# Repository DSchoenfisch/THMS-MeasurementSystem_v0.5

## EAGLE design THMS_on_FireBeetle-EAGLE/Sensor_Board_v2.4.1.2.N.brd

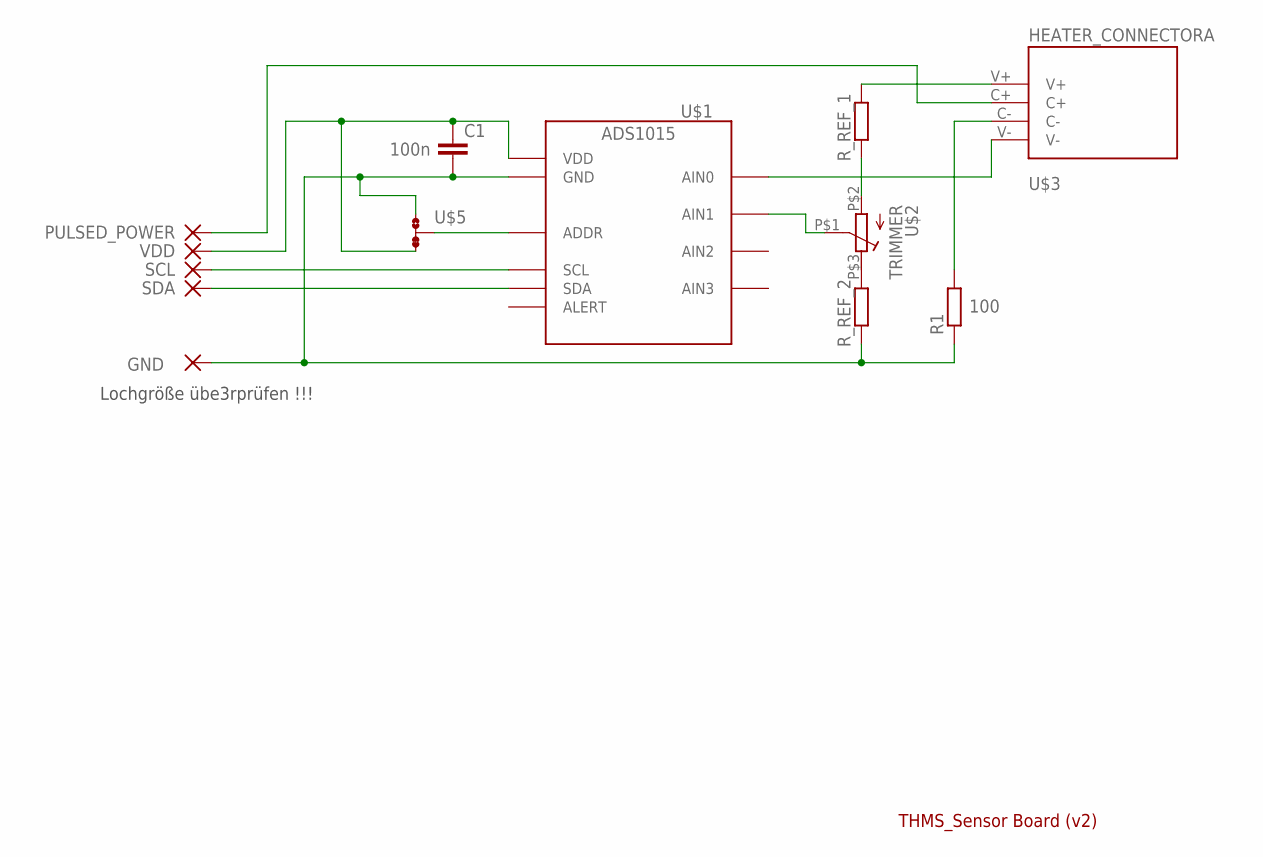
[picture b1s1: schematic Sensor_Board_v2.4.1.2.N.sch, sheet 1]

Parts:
C1: 100n; C0201
GND: 2,54/1,1
PULSED_POWER: SMD_PADSMD05-2(STPOO_DEFINED); SMD0,5-2(STOP_DEFINED)
R1: 100; R0402
R_REF_1, R_REF_2: 0; R0201
SCL: SMD_PADSMD05-2(STPOO_DEFINED); SMD0,5-2(STOP_DEFINED)
SDA: SMD_PADSMD05-2(STPOO_DEFINED); SMD0,5-2(STOP_DEFINED)
U$1: ADS1015; X2QFN10
U$2: TRIMMER; 2MM
U$3: HEATER_CONNECTORA; CONECTION_GATES
U$5: 0R-JUMP-1CON; D0R-JMP(D)
VDD: SMD_PADSMD05-2(STPOO_DEFINED); SMD0,5-2(STOP_DEFINED)

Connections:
GND: C1.2, GND.1, R1.1, R_REF_2.1, U$1.P$3 (GND), U$5.1; also elsewhere on the board
unnamed: R_REF_2.2, U$2.P$3 (A)
unnamed: SCL.1, U$1.P$10 (SCL)
unnamed: SDA.1, U$1.P$9 (SDA)
unnamed: R_REF_1.1, U$2.P$2 (E)
unnamed: R_REF_1.2, U$3.V+
unnamed: R1.2, U$3.C-
unnamed: PULSED_POWER.1, U$3.C+
unnamed: U$1.P$4 (AIN0), U$3.V-
unnamed: U$1.P$1 (ADDR), U$5.2
unnamed: U$1.P$5 (AIN1), U$2.P$1 (S)
VDD: C1.1, U$1.P$8 (VDD), U$5.3, VDD.1; also elsewhere on the board

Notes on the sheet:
Lochgröße übe3rprüfen !!!
THMS_Sensor Board (v2)

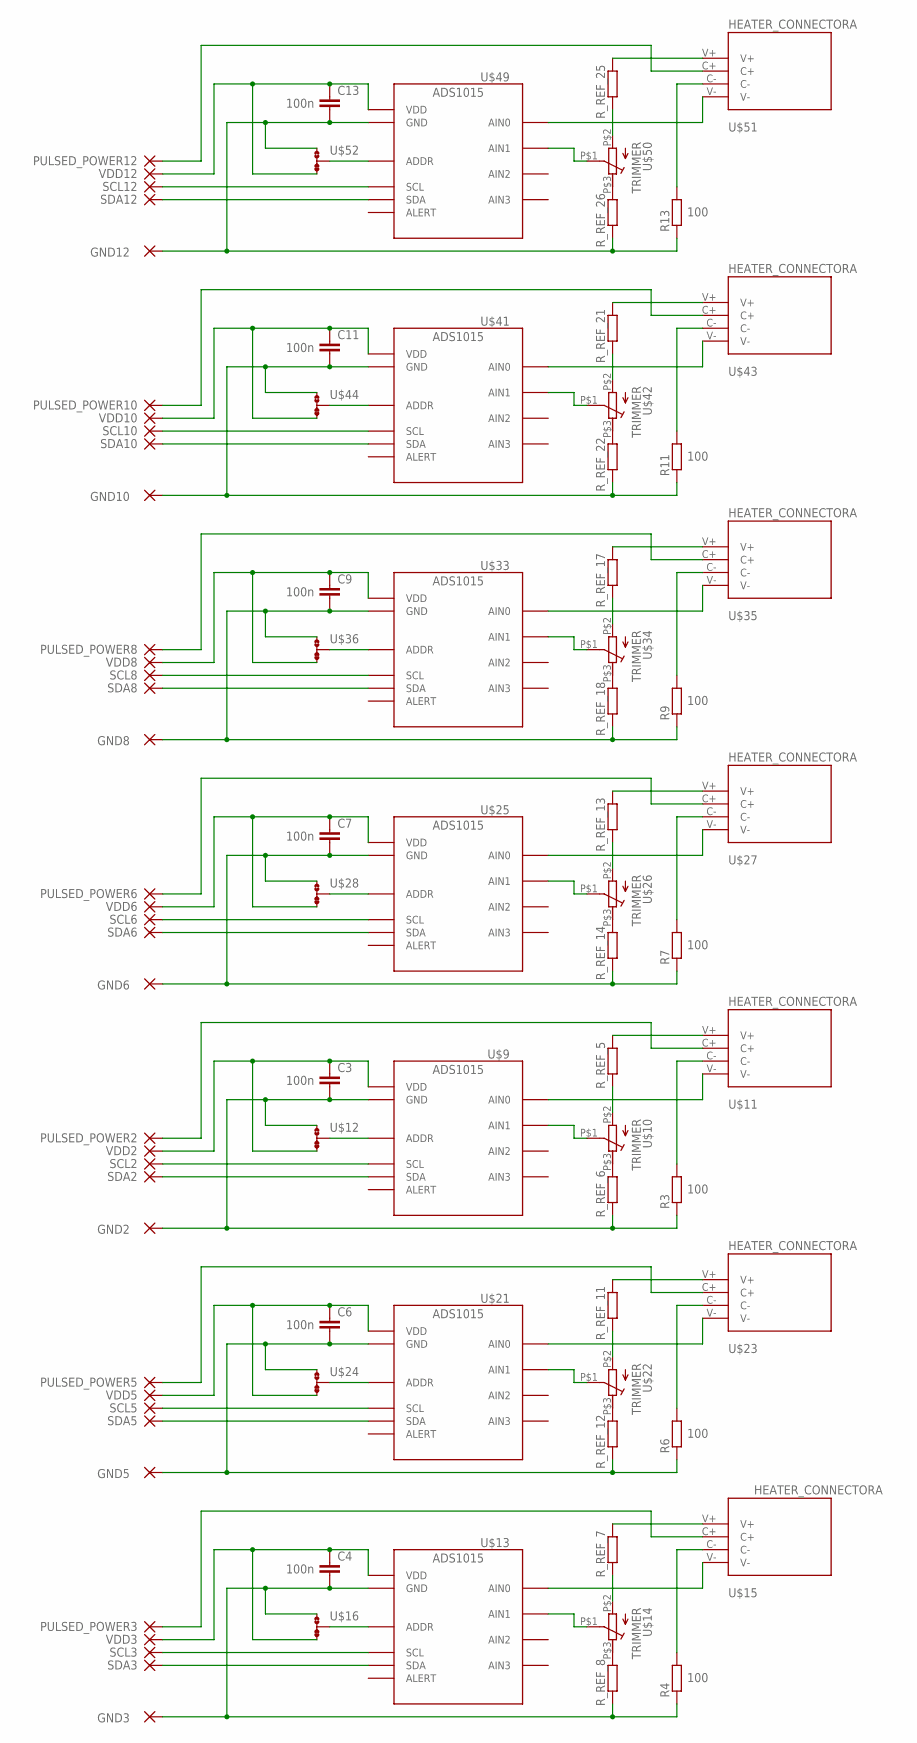
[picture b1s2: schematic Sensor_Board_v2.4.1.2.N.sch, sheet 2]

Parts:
C3, C4, C6, C7, C9, C11, C13: 100n; C0201
GND2, GND3, GND5, GND6, GND8, GND10, GND12: 2,54/1,1
PULSED_POWER2, PULSED_POWER3, PULSED_POWER5, PULSED_POWER6, PULSED_POWER8, PULSED_POWER10, PULSED_POWER12: SMD_PADSMD05-2(STPOO_DEFINED); SMD0,5-2(STOP_DEFINED)
R3, R4, R6, R7, R9, R11, R13: 100; R0402
R_REF_5, R_REF_6, R_REF_7, R_REF_8, R_REF_11, R_REF_12, R_REF_13, R_REF_14, R_REF_17, R_REF_18, R_REF_21, R_REF_22, R_REF_25, R_REF_26: 0; R0201
SCL2, SCL3, SCL5, SCL6, SCL8, SCL10, SCL12: SMD_PADSMD05-2(STPOO_DEFINED); SMD0,5-2(STOP_DEFINED)
SDA2, SDA3, SDA5, SDA6, SDA8, SDA10, SDA12: SMD_PADSMD05-2(STPOO_DEFINED); SMD0,5-2(STOP_DEFINED)
U$9, U$13, U$21, U$25, U$33, U$41, U$49: ADS1015; X2QFN10
U$10, U$14, U$22, U$26, U$34, U$42, U$50: TRIMMER; 2MM
U$11, U$15, U$23, U$27, U$35, U$43, U$51: HEATER_CONNECTORA; CONECTION_GATES
U$12, U$16, U$24, U$28, U$36, U$44, U$52: 0R-JUMP-1CON; D0R-JMP(D)
VDD2, VDD3, VDD5, VDD6, VDD8, VDD10, VDD12: SMD_PADSMD05-2(STPOO_DEFINED); SMD0,5-2(STOP_DEFINED)

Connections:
GND: C3.2, C4.2, C6.2, C7.2, C9.2, C11.2, C13.2, GND2.1, GND3.1, GND5.1, GND6.1, GND8.1, GND10.1, GND12.1, R3.1, R4.1, R6.1, R7.1, R9.1, R11.1, R13.1, R_REF_6.1, R_REF_8.1, R_REF_12.1, R_REF_14.1, R_REF_18.1, R_REF_22.1, R_REF_26.1, U$9.P$3 (GND), U$12.1, U$13.P$3 (GND), U$16.1, U$21.P$3 (GND), U$24.1, U$25.P$3 (GND), U$28.1, U$33.P$3 (GND), U$36.1, U$41.P$3 (GND), U$44.1, U$49.P$3 (GND), U$52.1; also elsewhere on the board
unnamed: SCL2.1, U$9.P$10 (SCL)
unnamed: SDA2.1, U$9.P$9 (SDA)
unnamed: R_REF_5.2, U$11.V+
unnamed: R3.2, U$11.C-
unnamed: U$9.P$4 (AIN0), U$11.V-
unnamed: PULSED_POWER2.1, U$11.C+
unnamed: U$9.P$5 (AIN1), U$10.P$1 (S)
unnamed: U$9.P$1 (ADDR), U$12.2
unnamed: R_REF_6.2, U$10.P$3 (A)
unnamed: R_REF_5.1, U$10.P$2 (E)
unnamed: SCL3.1, U$13.P$10 (SCL)
unnamed: SDA3.1, U$13.P$9 (SDA)
unnamed: R_REF_7.2, U$15.V+
unnamed: R4.2, U$15.C-
unnamed: U$13.P$4 (AIN0), U$15.V-
unnamed: PULSED_POWER3.1, U$15.C+
unnamed: U$13.P$5 (AIN1), U$14.P$1 (S)
unnamed: U$13.P$1 (ADDR), U$16.2
unnamed: R_REF_8.2, U$14.P$3 (A)
unnamed: R_REF_7.1, U$14.P$2 (E)
unnamed: SCL5.1, U$21.P$10 (SCL)
unnamed: SDA5.1, U$21.P$9 (SDA)
unnamed: R_REF_11.2, U$23.V+
unnamed: R6.2, U$23.C-
unnamed: U$21.P$4 (AIN0), U$23.V-
unnamed: PULSED_POWER5.1, U$23.C+
unnamed: U$21.P$5 (AIN1), U$22.P$1 (S)
unnamed: U$21.P$1 (ADDR), U$24.2
unnamed: R_REF_12.2, U$22.P$3 (A)
unnamed: R_REF_11.1, U$22.P$2 (E)
unnamed: SCL6.1, U$25.P$10 (SCL)
unnamed: SDA6.1, U$25.P$9 (SDA)
unnamed: R_REF_13.2, U$27.V+
unnamed: R7.2, U$27.C-
unnamed: U$25.P$4 (AIN0), U$27.V-
unnamed: PULSED_POWER6.1, U$27.C+
unnamed: U$25.P$5 (AIN1), U$26.P$1 (S)
unnamed: U$25.P$1 (ADDR), U$28.2
unnamed: R_REF_14.2, U$26.P$3 (A)
unnamed: R_REF_13.1, U$26.P$2 (E)
unnamed: SCL8.1, U$33.P$10 (SCL)
unnamed: SDA8.1, U$33.P$9 (SDA)
unnamed: R_REF_17.2, U$35.V+
unnamed: R9.2, U$35.C-
unnamed: U$33.P$4 (AIN0), U$35.V-
unnamed: PULSED_POWER8.1, U$35.C+
unnamed: U$33.P$5 (AIN1), U$34.P$1 (S)
unnamed: U$33.P$1 (ADDR), U$36.2
unnamed: R_REF_18.2, U$34.P$3 (A)
unnamed: R_REF_17.1, U$34.P$2 (E)
unnamed: SCL10.1, U$41.P$10 (SCL)
unnamed: SDA10.1, U$41.P$9 (SDA)
unnamed: R_REF_21.2, U$43.V+
unnamed: R11.2, U$43.C-
unnamed: U$41.P$4 (AIN0), U$43.V-
unnamed: PULSED_POWER10.1, U$43.C+
unnamed: U$41.P$5 (AIN1), U$42.P$1 (S)
unnamed: U$41.P$1 (ADDR), U$44.2
unnamed: R_REF_22.2, U$42.P$3 (A)
unnamed: R_REF_21.1, U$42.P$2 (E)
unnamed: SCL12.1, U$49.P$10 (SCL)
unnamed: SDA12.1, U$49.P$9 (SDA)
unnamed: R_REF_25.2, U$51.V+
unnamed: R13.2, U$51.C-
unnamed: U$49.P$4 (AIN0), U$51.V-
unnamed: PULSED_POWER12.1, U$51.C+
unnamed: U$49.P$5 (AIN1), U$50.P$1 (S)
unnamed: U$49.P$1 (ADDR), U$52.2
unnamed: R_REF_26.2, U$50.P$3 (A)
unnamed: R_REF_25.1, U$50.P$2 (E)
VDD: C3.1, C4.1, C6.1, C7.1, C9.1, C11.1, C13.1, U$9.P$8 (VDD), U$12.3, U$13.P$8 (VDD), U$16.3, U$21.P$8 (VDD), U$24.3, U$25.P$8 (VDD), U$28.3, U$33.P$8 (VDD), U$36.3, U$41.P$8 (VDD), U$44.3, U$49.P$8 (VDD), U$52.3, VDD2.1, VDD3.1, VDD5.1, VDD6.1, VDD8.1, VDD10.1, VDD12.1; also elsewhere on the board

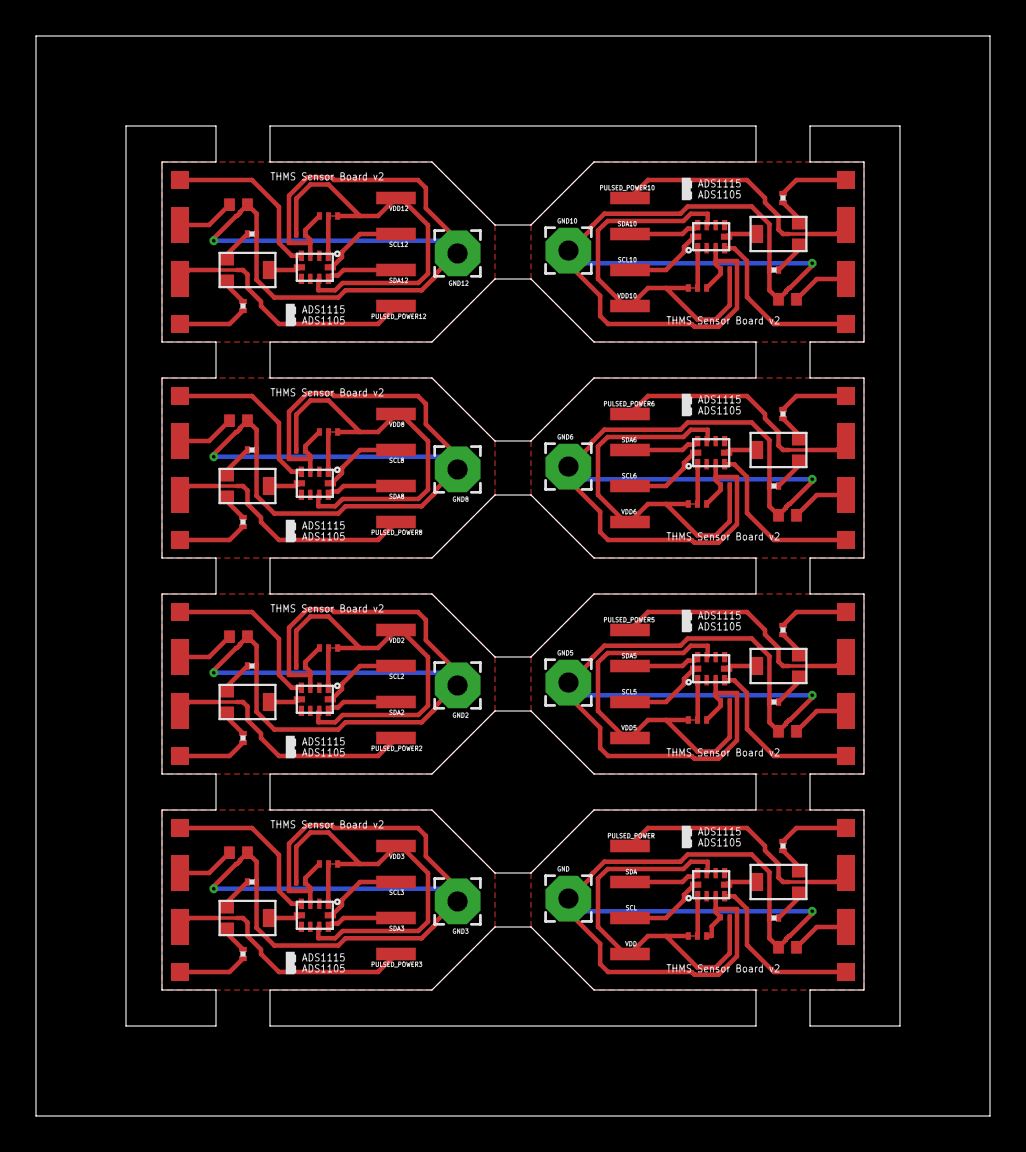
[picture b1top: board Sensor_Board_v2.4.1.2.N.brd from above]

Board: 2 copper layers, 53.0 x 60.0 mm, 104 parts (0 on the bottom side), 82 nets.

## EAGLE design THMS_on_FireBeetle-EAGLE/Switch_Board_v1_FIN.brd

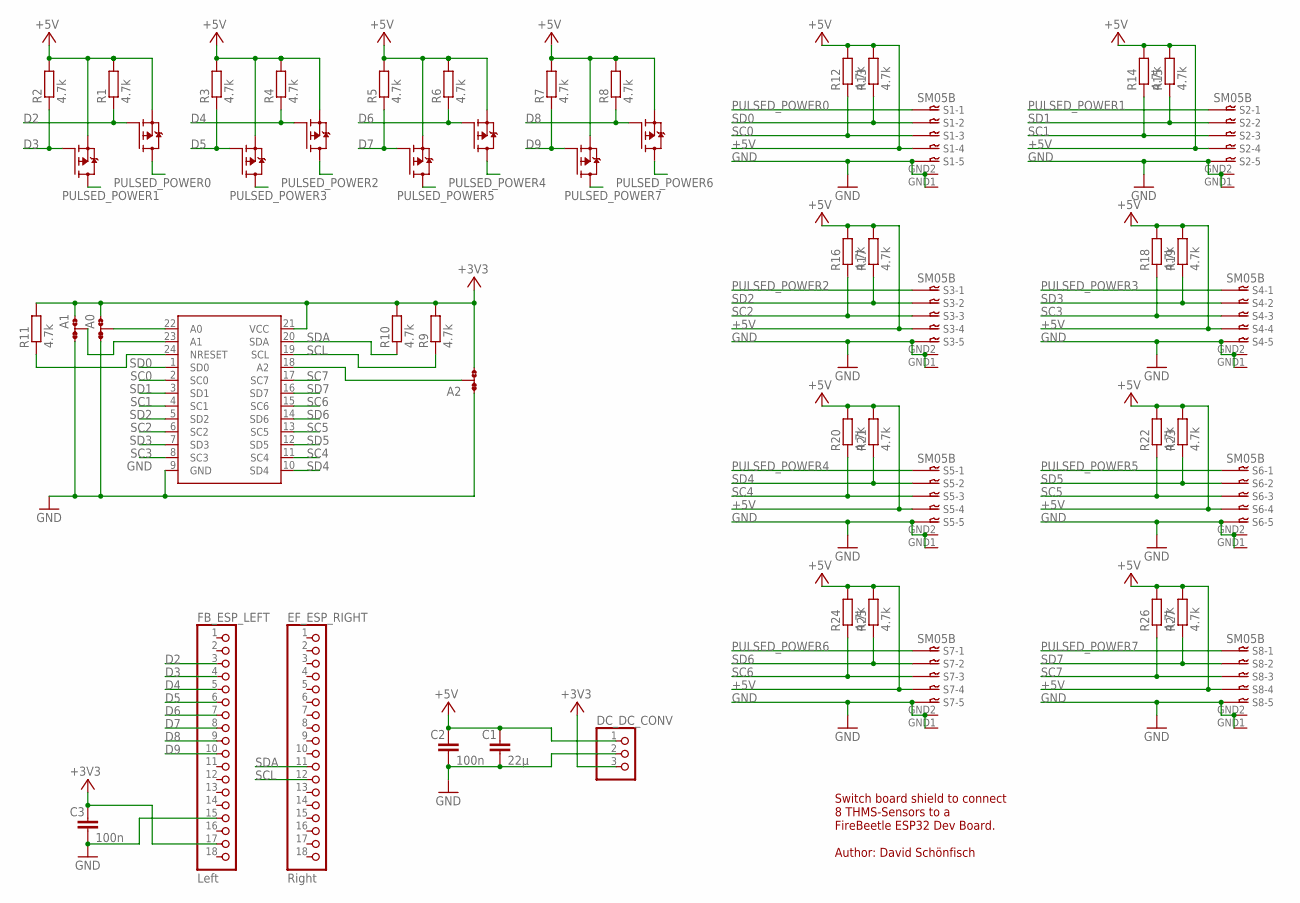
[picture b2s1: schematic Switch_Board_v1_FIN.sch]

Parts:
A0, A1, A2: 0R-JUMP-1CON; D0R-JMP(D)
C1: 22µ; C0603
C2, C3: 100n; C0603
DC_DC_CONV: 0; 1X03
EF_ESP_RIGHT: Right; 1X18
FB_ESP_LEFT: Left; 1X18
R1, R2, R3, R4, R5, R6, R7, R8, R9, R10, R11, R12, R13, R14, R15, R16, R17, R18, R19, R20, R21, R22, R23, R24, R25, R26, R27: 4.7k; R0603
S1, S2, S3, S4, S5, S6, S7, S8: SM05B
U$1: TCA9548PVQFN; S-PVQFN-N24
U$2, U$3, U$4, U$5: UM6J1N; SOT363_INFINEON

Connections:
+3V3: A0.1, A1.1, A2.1, C3.1, DC_DC_CONV.3, FB_ESP_LEFT.17, R9.2, R10.2, R11.2, U$1.21 (VCC)
+5V: C1.1, C2.1, DC_DC_CONV.1, R1.2, R2.2, R3.2, R4.2, R5.2, R6.2, R7.2, R8.2, R12.2, R13.2, R14.2, R15.2, R16.2, R17.2, R18.2, R19.2, R20.2, R21.2, R22.2, R23.2, R24.2, R25.2, R26.2, R27.2, S1.4 (1), S2.4 (1), S3.4 (1), S4.4 (1), S5.4 (1), S6.4 (1), S7.4 (1), S8.4 (1), U$2.1 (S), U$2.4 (S), U$3.1 (S), U$3.4 (S), U$4.1 (S), U$4.4 (S), U$5.1 (S), U$5.4 (S)
A0: A0.2, U$1.22 (A0)
A1: A1.2, U$1.23 (A1)
A2: A2.2, U$1.18 (A2)
D2: FB_ESP_LEFT.3, R1.1, U$2.2 (G)
D3: FB_ESP_LEFT.4, R2.1, U$2.5 (G)
D4: FB_ESP_LEFT.5, R4.1, U$3.2 (G)
D5: FB_ESP_LEFT.6, R3.1, U$3.5 (G)
D6: FB_ESP_LEFT.7, R6.1, U$4.2 (G)
D7: FB_ESP_LEFT.8, R5.1, U$4.5 (G)
D8: FB_ESP_LEFT.9, R8.1, U$5.2 (G)
D9: FB_ESP_LEFT.10, R7.1, U$5.5 (G)
GND: A0.3, A1.3, A2.3, C1.2, C2.2, C3.2, DC_DC_CONV.2, FB_ESP_LEFT.15, S1.5 (1), S1.GND1, S1.GND2, S2.5 (1), S2.GND1, S2.GND2, S3.5 (1), S3.GND1, S3.GND2, S4.5 (1), S4.GND1, S4.GND2, S5.5 (1), S5.GND1, S5.GND2, S6.5 (1), S6.GND1, S6.GND2, S7.5 (1), S7.GND1, S7.GND2, S8.5 (1), S8.GND1, S8.GND2, U$1.9 (GND)
NRESET: R11.1, U$1.24 (NRESET)
PULSED_POWER0: S1.1, U$2.6 (D)
PULSED_POWER1: S2.1, U$2.3 (D)
PULSED_POWER2: S3.1, U$3.6 (D)
PULSED_POWER3: S4.1, U$3.3 (D)
PULSED_POWER4: S5.1, U$4.6 (D)
PULSED_POWER5: S6.1, U$4.3 (D)
PULSED_POWER6: S7.1, U$5.6 (D)
PULSED_POWER7: S8.1, U$5.3 (D)
SC0: R12.1, S1.3 (1), U$1.2 (SC0)
SC1: R14.1, S2.3 (1), U$1.4 (SC1)
SC2: R16.1, S3.3 (1), U$1.6 (SC2)
SC3: R18.1, S4.3 (1), U$1.8 (SC3)
SC4: R20.1, S5.3 (1), U$1.11 (SC4)
SC5: R22.1, S6.3 (1), U$1.13 (SC5)
SC6: R24.1, S7.3 (1), U$1.15 (SC6)
SC7: R26.1, S8.3 (1), U$1.17 (SC7)
SCL: EF_ESP_RIGHT.12, R9.1, U$1.19 (SCL)
SD0: R13.1, S1.2 (1), U$1.1 (SD0)
SD1: R15.1, S2.2 (1), U$1.3 (SD1)
SD2: R17.1, S3.2 (1), U$1.5 (SD2)
SD3: R19.1, S4.2 (1), U$1.7 (SD3)
SD4: R21.1, S5.2 (1), U$1.10 (SD4)
SD5: R23.1, S6.2 (1), U$1.12 (SD5)
SD6: R25.1, S7.2 (1), U$1.14 (SD6)
SD7: R27.1, S8.2 (1), U$1.16 (SD7)
SDA: EF_ESP_RIGHT.11, R10.1, U$1.20 (SDA)

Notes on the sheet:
Switch board shield to connect 8 THMS-Sensors to a FireBeetle ESP32 Dev Board. Author: David Schönfisch

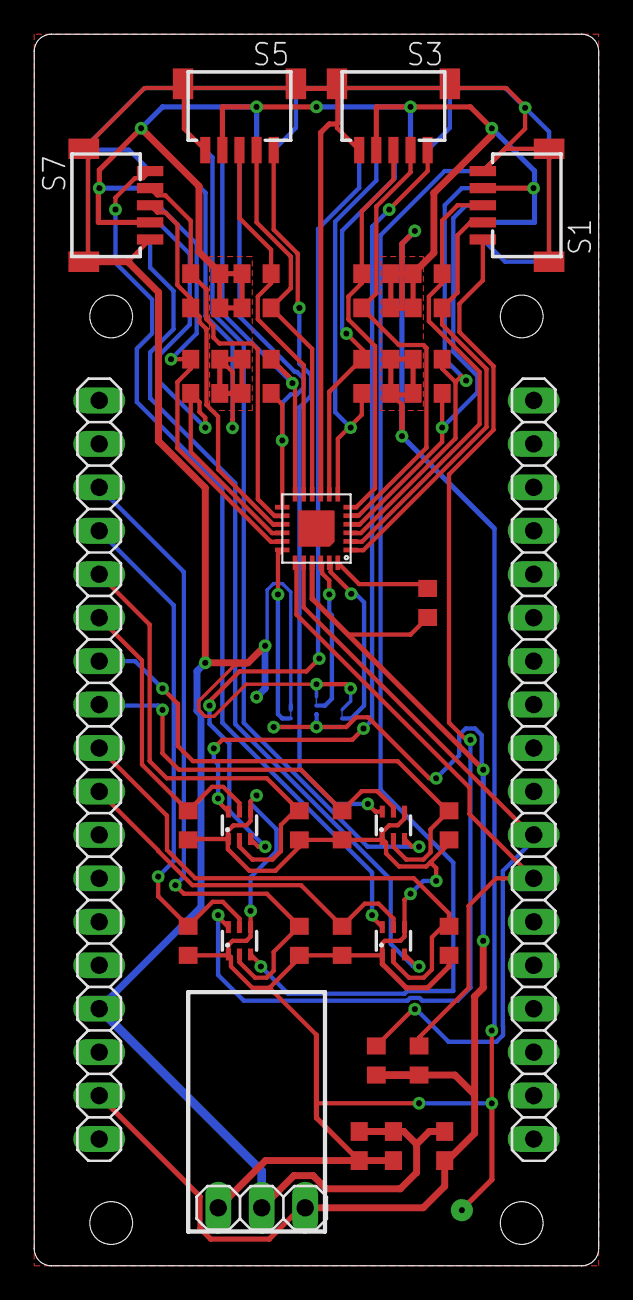
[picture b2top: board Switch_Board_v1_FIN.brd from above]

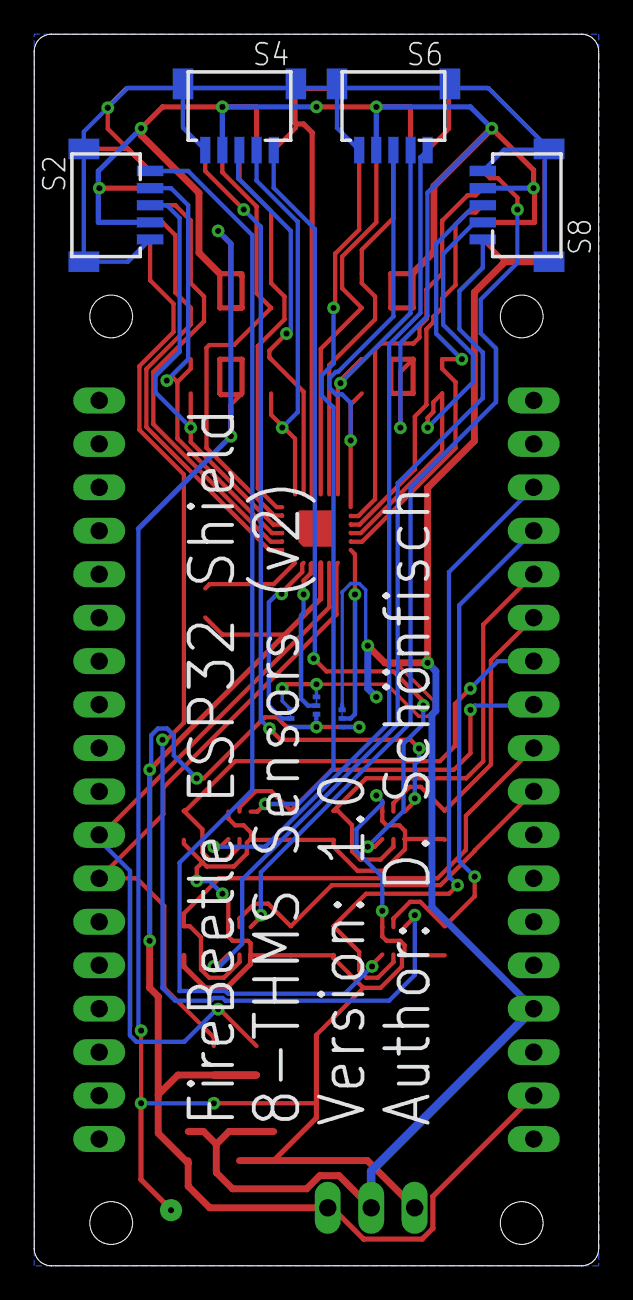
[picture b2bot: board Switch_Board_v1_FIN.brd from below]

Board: 2 copper layers, 33.0 x 72.0 mm, 49 parts (7 on the bottom side), 41 nets.
